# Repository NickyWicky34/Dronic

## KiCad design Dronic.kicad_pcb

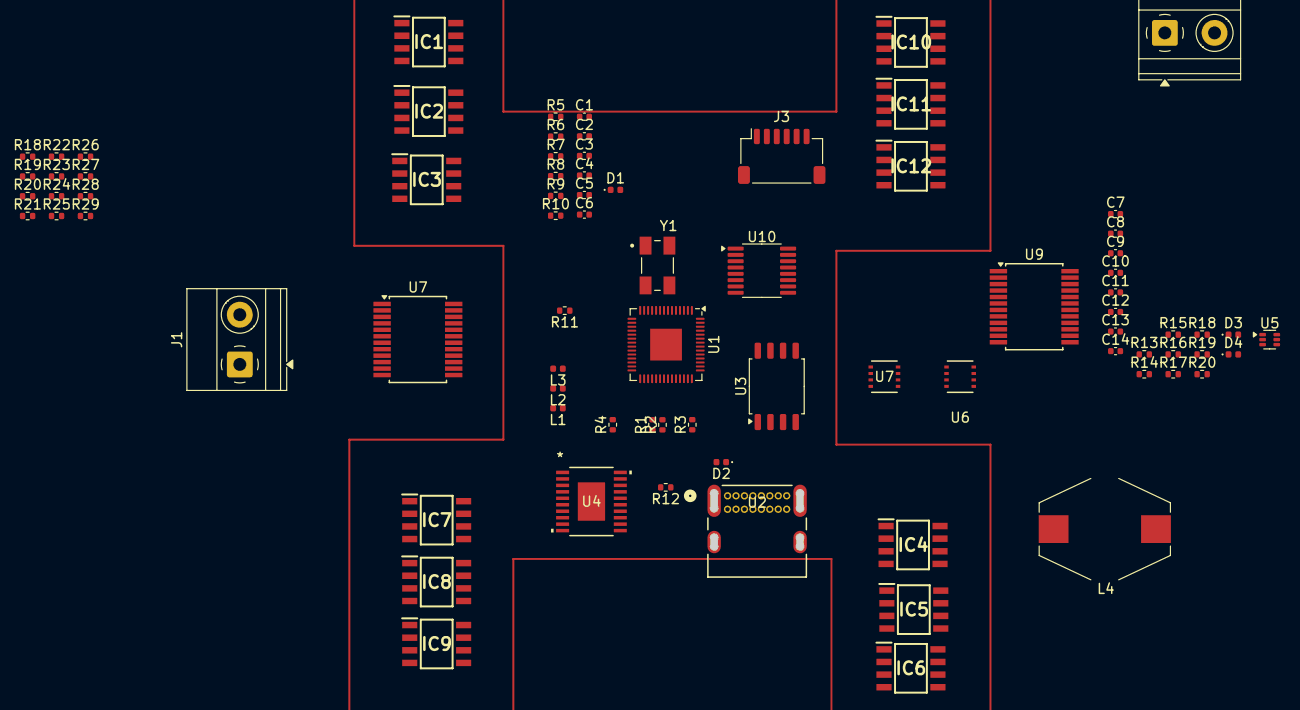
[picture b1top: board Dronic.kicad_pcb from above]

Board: 4 copper layers, 80 parts (0 on the bottom side), 91 nets, no tracks yet.

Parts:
C1, C2, C13: 10uF; C_0402_1005Metric
C3: 28uF; C_0402_1005Metric
C4, C14: 100nF; C_0402_1005Metric
C5, C6: 30pF; C_0402_1005Metric
C7, C8, C9, C10, C11, C12: 1uF; C_0402_1005Metric
D1, D2, D3, D4: D_Zener; D_0402_1005Metric
IC1, IC2, IC3, IC4, IC5, IC6, IC7, IC8, IC9, IC10, IC11, IC12: ACS71240LLCBTR-050U5; SOIC127P600X175-8N
J1: SWDIO_PH_TERM; TerminalBlock_Phoenix_MKDS-1,5-2_1x02_P5.00mm_Horizontal
J2: Screw_Terminal_01x02; TerminalBlock_Phoenix_MKDS-1,5-2_1x02_P5.00mm_Horizontal
J3: JST_SH_6P_1.00mm; JST_SH_SM06B-SRSS-TB_1x06-1MP_P1.00mm_Horizontal
L1, L2, L3: 4.7uH; L_0402_1005Metric
L4: 68uH; L_Bourns-SRR1005
R1, R2: 27; R_0402_1005Metric
R3, R4, R17, R18#2, R19, R20#2: 5.1K; R_0402_1005Metric
R5: 137K; R_0402_1005Metric
R6: 68.1K; R_0402_1005Metric
R7: 100k; R_0402_1005Metric
R8: 100K; R_0402_1005Metric
R9: 221K; R_0402_1005Metric
R10: 1.0M; R_0402_1005Metric
R11, R12: 0; R_0402_1005Metric
R13: 55K; R_0402_1005Metric
R14: 45K; R_0402_1005Metric
R15: 52.3K; R_0402_1005Metric
R16, R18, R19#2: 10K; R_0402_1005Metric
R20, R21, R22, R23, R24, R25, R26, R27, R28, R29: 5K; R_0402_1005Metric
U1: RP2040; QFN-56-1EP_7x7mm_P0.4mm_EP3.2x3.2mm
U2: 2137160001; 2137160001_MOL
U3: W25Q128JVS; SOIC-8_5.3x5.3mm_P1.27mm
U4: LTC3521EFE-PBF; TSSOP-20_FE&slash_CB_LIT
U5: AP62150WU; SOT-563
U6, U7: ECH8690-TL-H; ECH8_2P9X2P3_ONS
U7#2, U9: PCF8575DBR; SSOP-24_5.3x8.2mm_P0.65mm
U10: MAX11616; QSOP-16_3.9x4.9mm_P0.635mm
Y1: ABM3B-12.000MHZ-10-1-U-T; XTAL_ABM3B-12.000MHZ-10-1-U-T

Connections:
1.2V: C1.1, L3.2, R7.1
11.1V: C13.1, D3.2 (A), J2.2, R13.1
+1.8V: C2.1, L2.2, R5.1
+1V1: C10.1, C11.1, C12.1, U1.23 (DVDD), U1.45 (VREG_VOUT), U1.50 (DVDD)
+3.3V: C3.1, C4.1, J3.1, J3.2, R10.1, R11.1, R12.1, R22.1, R23.1, U3.8 (VCC), U4.16 (VOUT1), U7#2.1 (~INT), U7#2.24 (VCC), U9.1 (~INT), U9.21 (A0), U9.24 (VCC)
+M1_U: IC1.1 (IP+_1), IC1.2 (IP+_2)
+M1_V: IC2.1 (IP+_1), IC2.2 (IP+_2)
+M1_W: IC3.1 (IP+_1), IC3.2 (IP+_2)
+M2_U: IC7.1 (IP+_1), IC7.2 (IP+_2)
+M2_V: IC8.1 (IP+_1), IC8.2 (IP+_2)
+M2_W: IC9.1 (IP+_1), IC9.2 (IP+_2)
+M3_U: IC4.1 (IP+_1), IC4.2 (IP+_2)
+M3_V: IC5.1 (IP+_1), IC5.2 (IP+_2)
+M3_W: IC6.1 (IP+_1), IC6.2 (IP+_2)
+M4_U: IC10.1 (IP+_1), IC10.2 (IP+_2)
+M4_V: IC11.1 (IP+_1), IC11.2 (IP+_2)
+M4_W: IC12.1 (IP+_1), IC12.2 (IP+_2)
-M1_U: IC1.3 (IP-_1), IC1.4 (IP-_2)
-M1_V: IC2.3 (IP-_1), IC2.4 (IP-_2)
-M1_W: IC3.3 (IP-_1), IC3.4 (IP-_2)
-M2_U: IC7.3 (IP-_1), IC7.4 (IP-_2)
-M2_V: IC8.3 (IP-_1), IC8.4 (IP-_2)
-M2_W: IC9.3 (IP-_1), IC9.4 (IP-_2)
-M3_U: IC4.3 (IP-_1), IC4.4 (IP-_2)
-M3_V: IC5.3 (IP-_1), IC5.4 (IP-_2)
-M3_W: IC6.3 (IP-_1), IC6.4 (IP-_2)
-M4_U: IC10.3 (IP-_1), IC10.4 (IP-_2)
-M4_V: IC11.3 (IP-_1), IC11.4 (IP-_2)
-M4_W: IC12.3 (IP-_1), IC12.4 (IP-_2)
ADC_SCL: R28.2, U10.13 (SCL)
ADC_SDA: R29.2, U10.14 (SDA)
AIN0: IC1.7 (VIOUT), U10.5 (AIN0)
AIN1: IC2.7 (VIOUT), U10.6 (AIN1)
AIN2: IC3.7 (VIOUT), U10.7 (AIN2)
AIN3: IC7.7 (VIOUT), U10.8 (AIN3)
AIN4: IC8.7 (VIOUT), U10.9 (AIN4)
AIN5: IC9.7 (VIOUT), U10.10 (AIN5)
AIN6: IC4.7 (VIOUT), U10.11 (AIN6)
AIN7: IC5.7 (VIOUT), U10.12 (AIN7)
AIN8: IC6.7 (VIOUT), U10.4 (AIN8)
AIN9: IC10.7 (VIOUT), U10.3 (AIN9)
AIN10: IC11.7 (VIOUT), U10.2 (AIN10)
AIN11: IC12.7 (VIOUT), U10.1 (AIN11)
DN: R2.1, U2.A7 (DN1), U2.B7 (DN2)
DP: R1.1, U2.A6 (DP1), U2.B6 (DP2)
GND: C1.2, C2.2, C3.2, C4.2, C5.2, C6.2, C13.2, C14.2, D2.2 (A), IC1.5 (GND), IC2.5 (GND), IC3.5 (GND), IC4.5 (GND), IC5.5 (GND), IC6.5 (GND), IC7.5 (GND), IC8.5 (GND), IC9.5 (GND), IC10.5 (GND), IC11.5 (GND), IC12.5 (GND), J2.1, J3.6, R3.2, R4.2, R6.2, R8.2, R9.2, R14.2, R16.2, R18.2, R18#2.2, R19#2.2, R20#2.2, U1.19 (TESTEN), U1.57 (GND), U2.A1 (GND), U2.A12 (GND), U2.B1 (GND), U2.B12 (GND), U3.4 (GND), U4.8 (GND), U4.18 (PGND2), U4.EPAD, U5.1 (GND), U7#2.2 (A1), U7#2.3 (A2), U7#2.12 (GND), U7#2.21 (A0), U9.2 (A1), U9.3 (A2), U9.12 (GND), U10.15 (GND), Y1.2 (GND), Y1.4 (GND)
IO0: U1.53 (QSPI_SD0), U3.5 (DI/IO_{0})
IO1: U1.55 (QSPI_SD1), U3.2 (DO/IO_{1})
IO2: U1.54 (QSPI_SD2), U3.3 (~WP/IO_{2})
IO3: U1.51 (QSPI_SD3), U3.7 (~HOLD/~RESET/IO_{3})
MEM_CLK: U1.52 (QSPI_SCLK), U3.6 (CLK)
MOTOR_SCL: R23.2, U7#2.23 (SDA), U9.23 (SDA)
MOTOR_SDA: R22.2, U7#2.22 (SCL), U9.22 (SCL)
unnamed: C7.2, C8.2, C9.2
unnamed: C10.2, C11.2, C12.2
unnamed: D1.1 (K), U4.7 (VIN), U4.13 (PVIN1), U4.20 (PVIN2)
unnamed: D3.1 (K), U5.3 (VIN)
unnamed: J1.1, U1.25 (SWD)
unnamed: J1.2, U1.24 (SWCLK)
unnamed: R2.2, U1.46 (USB_DM)
unnamed: R1.2, U1.47 (USB_DP)
unnamed: R4.1, U2.A5 (CC1)
unnamed: R3.1, U2.B5 (CC2)
unnamed: R9.1, R10.2, U4.10 (FB1)
unnamed: R5.2, R6.1, U4.2 (FB2)
unnamed: R7.2, R8.1, U4.1 (FB3)
unnamed: L1.2, U4.15 (SW1A)
unnamed: L1.1, U4.14 (SW1B)
unnamed: L2.1, U4.19 (SW2)
unnamed: L3.1, U4.17 (SW3)
unnamed: C14.1, U5.6 (BST)
unnamed: R13.2, R14.1, U5.5 (EN)
unnamed: R15.2, R16.1, U5.4 (FB)
unnamed: L4.1, U5.2 (SW)
unnamed: R17.2, U6.2 (Gate1)
unnamed: R19.2, U7.2 (Gate1)
unnamed: R20#2.1, U7.4 (Gate2)
SCL: J3.4, R21.2, R25.2, R27.2, U1.12 (GPIO9)
SDA: J3.3, R20.2, R24.2, R26.2, U1.11 (GPIO8)
SS: U1.56 (QSPI_SS), U3.1 (~CS)
TFS20_CS: J3.5, U1.13 (GPIO10)
U7_P6: IC1.6 (~FAULT), IC2.6 (~FAULT), IC3.6 (~FAULT), U7#2.10 (P6)
U7_P7: IC7.6 (~FAULT), IC8.6 (~FAULT), IC9.6 (~FAULT), U7#2.11 (P7)
U8_P6: IC4.6 (~FAULT), IC5.6 (~FAULT), IC6.6 (~FAULT), U9.10 (P6)
U8_P7: IC10.6 (~FAULT), IC11.6 (~FAULT), IC12.6 (~FAULT), U9.11 (P7)
VBAT_REG: D4.1 (K), D4.2 (A), IC1.8 (VCC), IC2.8 (VCC), IC3.8 (VCC), IC4.8 (VCC), IC5.8 (VCC), IC6.8 (VCC), IC7.8 (VCC), IC8.8 (VCC), IC9.8 (VCC), IC10.8 (VCC), IC11.8 (VCC), IC12.8 (VCC), L4.2, R15.1, R28.1, R29.1, U6.1 (Source1), U7.1 (Source1), U10.16 (Vdd)
VBUS: D2.1 (K), R17.1, R19.1, U2.A4 (VBUS), U2.A9 (VBUS), U2.B4 (VBUS), U2.B9 (VBUS), U4.3 (*SHDN2), U4.9 (PWM), U4.11 (*SHDN3), U4.12 (*SHDN1), U6.3 (Source2), U7.3 (Source2)
VCC: C7.1, C8.1, C9.1, R20.1, R21.1, R24.1, R25.1, R26.1, R27.1, U1.1 (IOVDD), U1.10 (IOVDD), U1.22 (IOVDD), U1.33 (IOVDD), U1.42 (IOVDD), U1.43 (ADC_AVDD), U1.44 (VREG_IN), U1.48 (USB_VDD), U1.49 (IOVDD), U7.5 (Drain2), U7.6 (Drain2), U7.7 (Drain1), U7.8 (Drain1)
VDD: D1.2 (A), U6.5 (Drain2), U6.6 (Drain2), U6.7 (Drain1), U6.8 (Drain1)
XIN: C5.1, U1.20 (XIN), Y1.1
XOUT: C6.1, U1.21 (XOUT), Y1.3

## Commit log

2025-05-02 Main File Push
2025-05-02 SM06B-SRSS-TB 6 Pin Connector Male, this will be used for the Benewake TFS20-L LiDAR Module
2025-05-02 SM06B-SRSS-TB 6 Pin Connector Male, this will be used for the Benewake TFS20-L LiDAR Module For Real This Time
2025-05-02 Schematic Updates
2025-05-02 Adding Additional Files Check
2025-05-02 Tiny Schematic Update Push to Cloud
2025-05-04 Updates, intending on using the PCD8575 for I2C Motor Control
2025-05-06 Motor Controller Update
2025-05-06 Title and Clean Up
2025-05-06 Added new parts, Edited Schematic
2025-05-07 Schematic Clean-Up and added XBEE Module
2025-05-07 Added screenshot of pinout for XBEE
2025-05-07 Edits
